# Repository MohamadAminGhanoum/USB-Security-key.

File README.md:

# USB-Security-key.
I want to make this key a type-c key, which i can use to log into my computer or account with for better security. (at the end i had to use USB-A)

So i initially started with making this a usb-c security key, because i would be able to use it on all my devices, however, since the thickness of the board would need to be around 1.6 mm, it would cost too much in jlcpcb, therefore i had to disregard this idea, and move to a usb-type a port. I also wanted this to be assembled by jlcpcb, but since the components are on both sides of the board, it would cost approximately 105 usd to only assemble the board. 

Therefore i came with the idea that i would like to use a high melting solder on the side with least components, and the other side, i want to use solder that will melt in the temperature of around 180 degrees.

## Built version:

## 3d-model

## Schematics:

## pcb

## BOM

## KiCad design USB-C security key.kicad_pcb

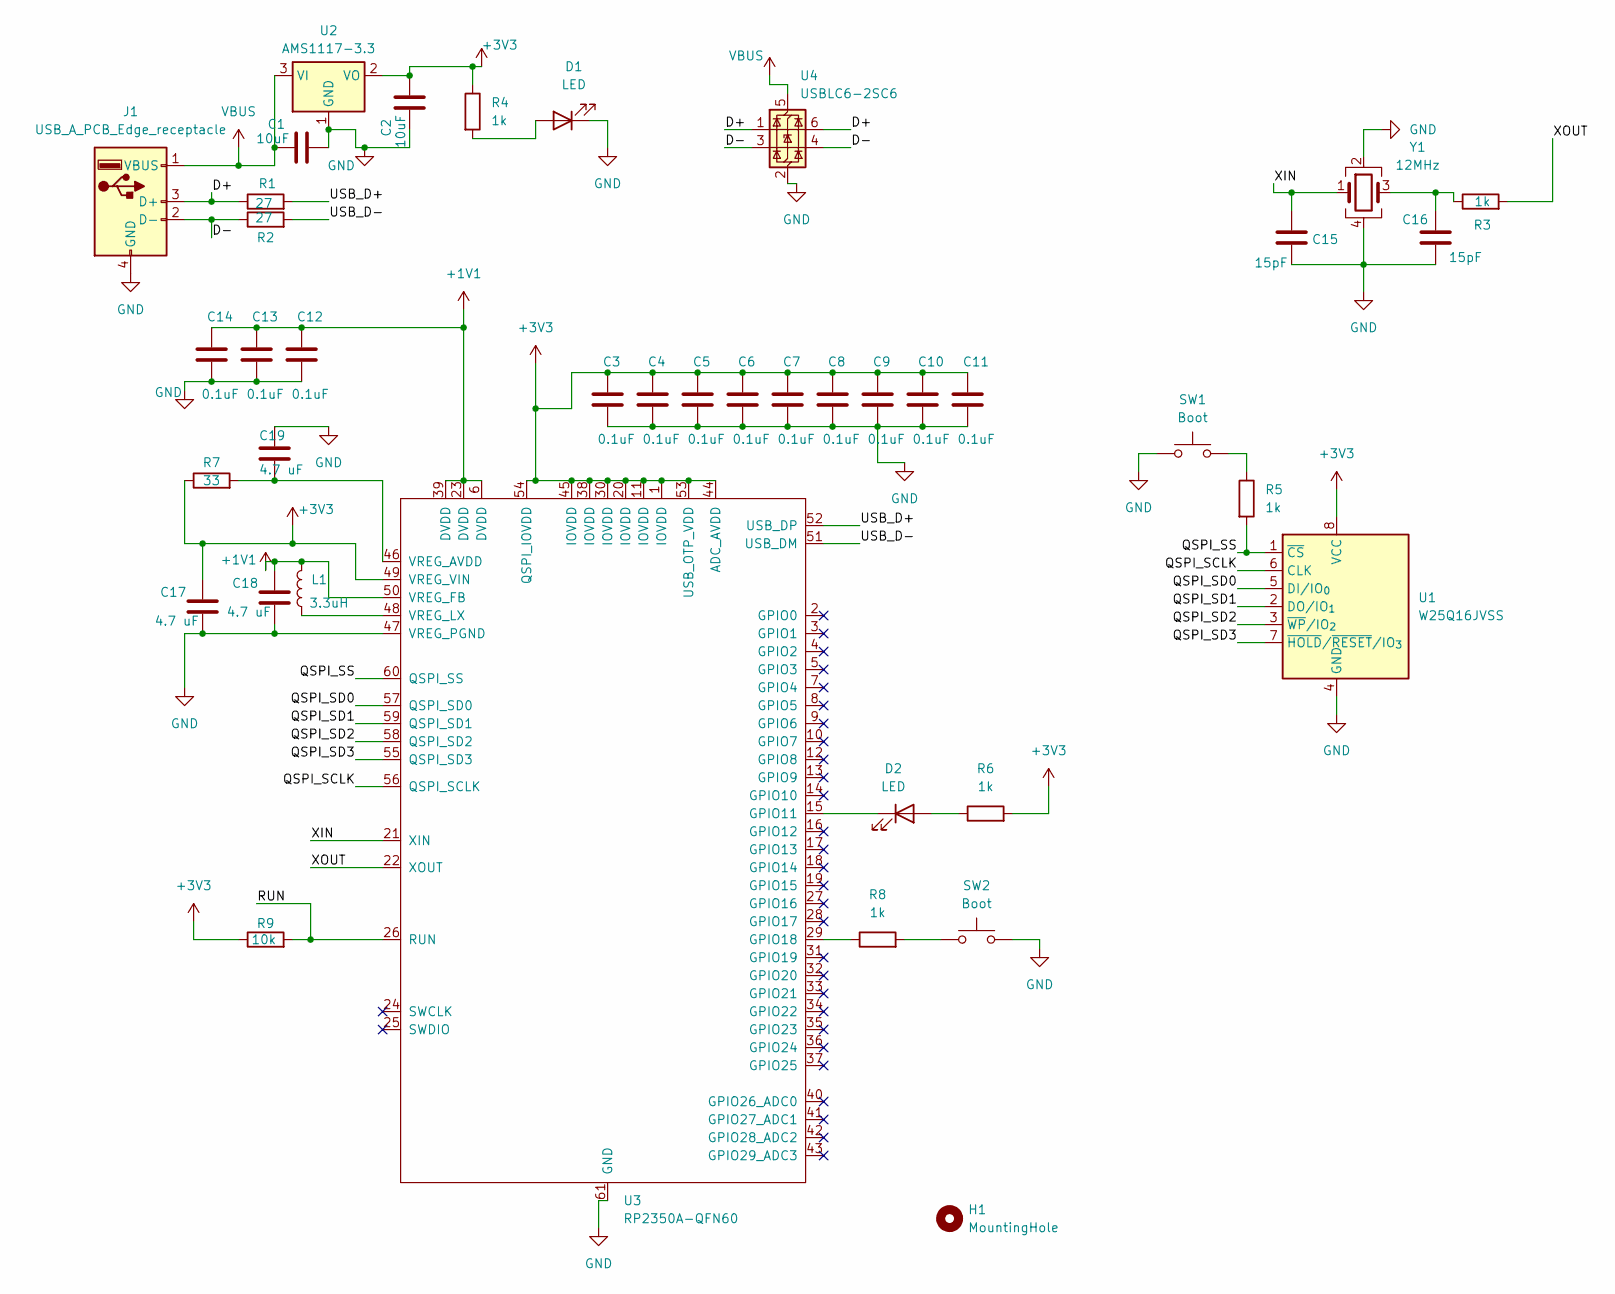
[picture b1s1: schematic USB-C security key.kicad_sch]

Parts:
C1, C2: 10uF; C_0603_1608Metric
C3, C4, C5, C6, C7, C8, C9, C10, C11, C12, C13, C14: 0.1uF; C_0603_1608Metric
C15, C16: 15pF; C_0603_1608Metric
C17, C18, C19: 4.7 uF; C_0603_1608Metric
D1, D2: LED; LED_0603_1608Metric
H1: MountingHole; MountingHole_2.1mm
J1: USB_A_PCB_Edge_receptacle
L1: 3.3uH; L_0603_1608Metric
R1, R2: 27; R_0603_1608Metric
R3, R4, R5, R6, R8: 1k; R_0603_1608Metric
R7: 33; R_0603_1608Metric
R9: 10k; R_0603_1608Metric
SW1, SW2: Boot; SW_Push_SPST_NO_Alps_SKRK
U1: W25Q16JVSS; SOIC-8_5.3x5.3mm_P1.27mm
U2: AMS1117-3.3; SOT-223-3_TabPin2
U3: RP2350A-QFN60; QFN-60-1EP_7x7mm_P0.4mm_EP3.4x3.4mm_ThermalVias
U4: USBLC6-2SC6; SOT-23-6
Y1: 12MHz; Crystal_SMD_3225-4Pin_3.2x2.5mm

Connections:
+1V1: C12.1, C13.1, C14.1, C18.1, L1.2, U3.6 (DVDD), U3.23 (DVDD), U3.39 (DVDD), U3.50 (VREG_FB)
+3V3: C2.2, C3.1, C4.1, C5.1, C6.1, C7.1, C8.1, C9.1, C10.1, C11.1, C17.1, R4.1, R6.2, R7.1, R9.1, U1.8 (VCC), U2.2 (VO), U3.1 (IOVDD), U3.11 (IOVDD), U3.20 (IOVDD), U3.30 (IOVDD), U3.38 (IOVDD), U3.44 (ADC_AVDD), U3.45 (IOVDD), U3.49 (VREG_VIN), U3.53 (USB_OTP_VDD), U3.54 (QSPI_IOVDD)
/D+: J1.3 (D+), R1.1, U4.1 (I/O1), U4.6 (I/O1)
/D-: J1.2 (D-), R2.1, U4.3 (I/O2), U4.4 (I/O2)
/QSPI_SCLK: U1.6 (CLK), U3.56 (QSPI_SCLK)
/QSPI_SD0: U1.5 (DI/IO_{0}), U3.57 (QSPI_SD0)
/QSPI_SD1: U1.2 (DO/IO_{1}), U3.59 (QSPI_SD1)
/QSPI_SD2: U1.3 (~WP/IO_{2}), U3.58 (QSPI_SD2)
/QSPI_SD3: U1.7 (~HOLD/~RESET/IO_{3}), U3.55 (QSPI_SD3)
/QSPI_SS: R5.2, U1.1 (~CS), U3.60 (QSPI_SS)
/RUN: R9.2, U3.26 (RUN)
/USB_D+: R1.2, U3.52 (USB_DP)
/USB_D-: R2.2, U3.51 (USB_DM)
/XIN: C15.1, U3.21 (XIN), Y1.1
/XOUT: R3.2, U3.22 (XOUT)
GND: C1.2, C2.1, C3.2, C4.2, C5.2, C6.2, C7.2, C8.2, C9.2, C10.2, C11.2, C12.2, C13.2, C14.2, C15.2, C16.2, C17.2, C18.2, C19.1, D1.1 (K), J1.4 (GND), SW1.1, SW2.2, U1.4 (GND), U2.1 (GND), U3.47 (VREG_PGND), U3.61 (GND), U4.2 (GND), Y1.2, Y1.4
unnamed: C16.1, R3.1, Y1.3
unnamed: D1.2 (A), R4.2
unnamed: D2.2 (A), R6.1
unnamed: D2.1 (K), U3.15 (GPIO11)
unnamed: R5.1, SW1.2
unnamed: R8.2, SW2.1
unnamed: R8.1, U3.29 (GPIO18)
unnamed: C19.2, R7.2, U3.46 (VREG_AVDD)
unnamed: L1.1, U3.48 (VREG_LX)
VBUS: C1.1, J1.1 (VBUS), U2.3 (VI), U4.5 (VBUS)

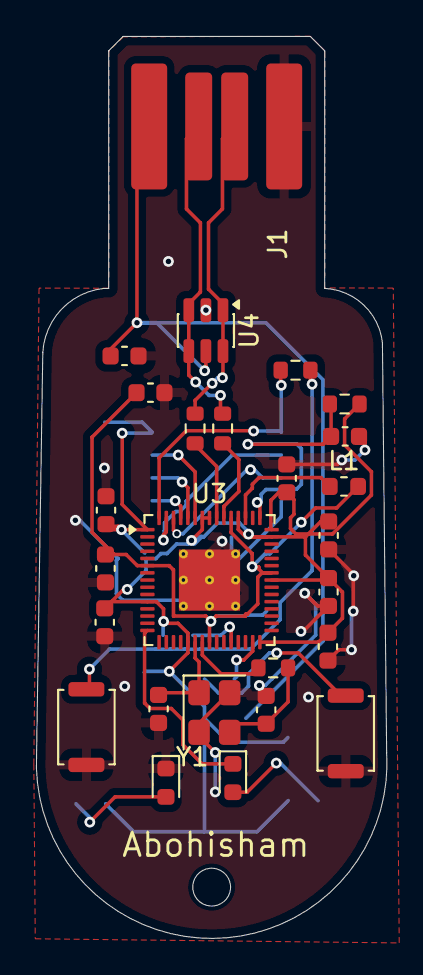
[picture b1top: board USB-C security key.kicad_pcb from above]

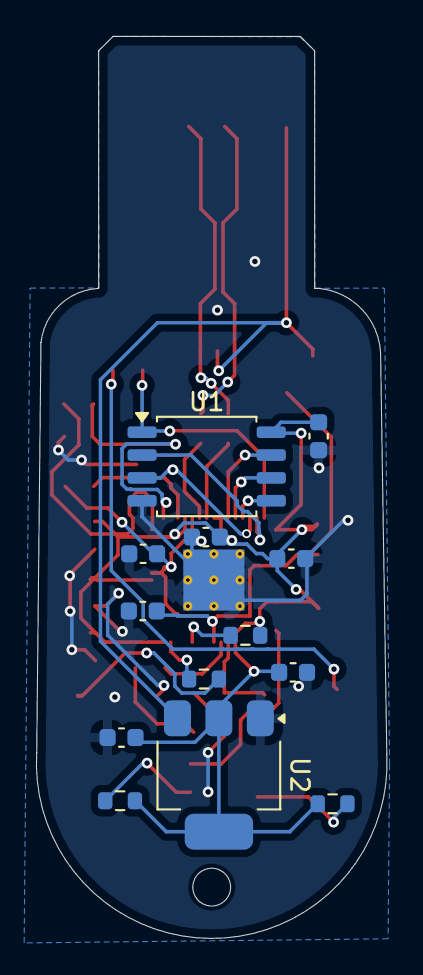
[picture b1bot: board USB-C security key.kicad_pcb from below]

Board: 2 copper layers, 19.5 x 50.1 mm, 40 parts (13 on the bottom side), 26 nets.

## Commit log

2026-03-29 Rename USB-C security key.kicad_pcb to Kicad&PCB/USB-C security key.kicad_pcb
2026-03-29 Rename Gerbers-UsbCSecurity.zip to Production/Gerbers-UsbCSecurity.zip
2026-06-14 Update README with built version and 3D model
    Added built version and 3D model images to README.
2026-06-14 Fix duplicate image in README
    Removed duplicate image entry in README.
